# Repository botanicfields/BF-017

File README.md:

# BF-017
タイマーIC 555をディスクリート・トランジスタで作る基板

頒布(Martket place):
https://www.switch-science.com/catalog/6433/

Qiitaに説明があります。
https://qiita.com/BotanicFields/items/ccec29255a49967116c1

GitHubに資料があります。
https://github.com/botanicfields/BF-017

AkiCart:
https://aki.prioris.jp/list/0b58d2fc-eee4-429c-9d86-0e2e1c66c018/

### はじめに
　古典的なタイマーICである555の内部回路を、単体（ディスクリート）トランジスタで実現するプリント基板を作成しました。中国の製造業者がプリント基板を安価かつ短納期で試作してくれます。個人でもプリント基板の設計発注が容易になっていて、555はトレーニングに適切な題材と思いました。

### 工夫点
　オシロスコープによる波形観測を容易にするためにテストポイントを設けます。トランジスタや抵抗などの部品の足やパッドから信号を取り出す必要がなくなり部品を比較的詰めて配置できます。
 
### お詫び
　プリント基板のシルク印刷でQ10, Q11, Q12, Q13の位置を間違えています。幸い、いずれも同じPNPトランジスタなので結果的に組立時には問題にはなりません。
V01L02で修正しました。資料は訂正済のものです。正しくは資料を参照ください。

https://github.com/botanicfields/BF-017/blob/master/BF-017_POS.pdf

### 提供元
BotanicFields, Inc.

https://www.facebook.com/botanicfields/

https://twitter.com/botanicfields

2020年6月22日

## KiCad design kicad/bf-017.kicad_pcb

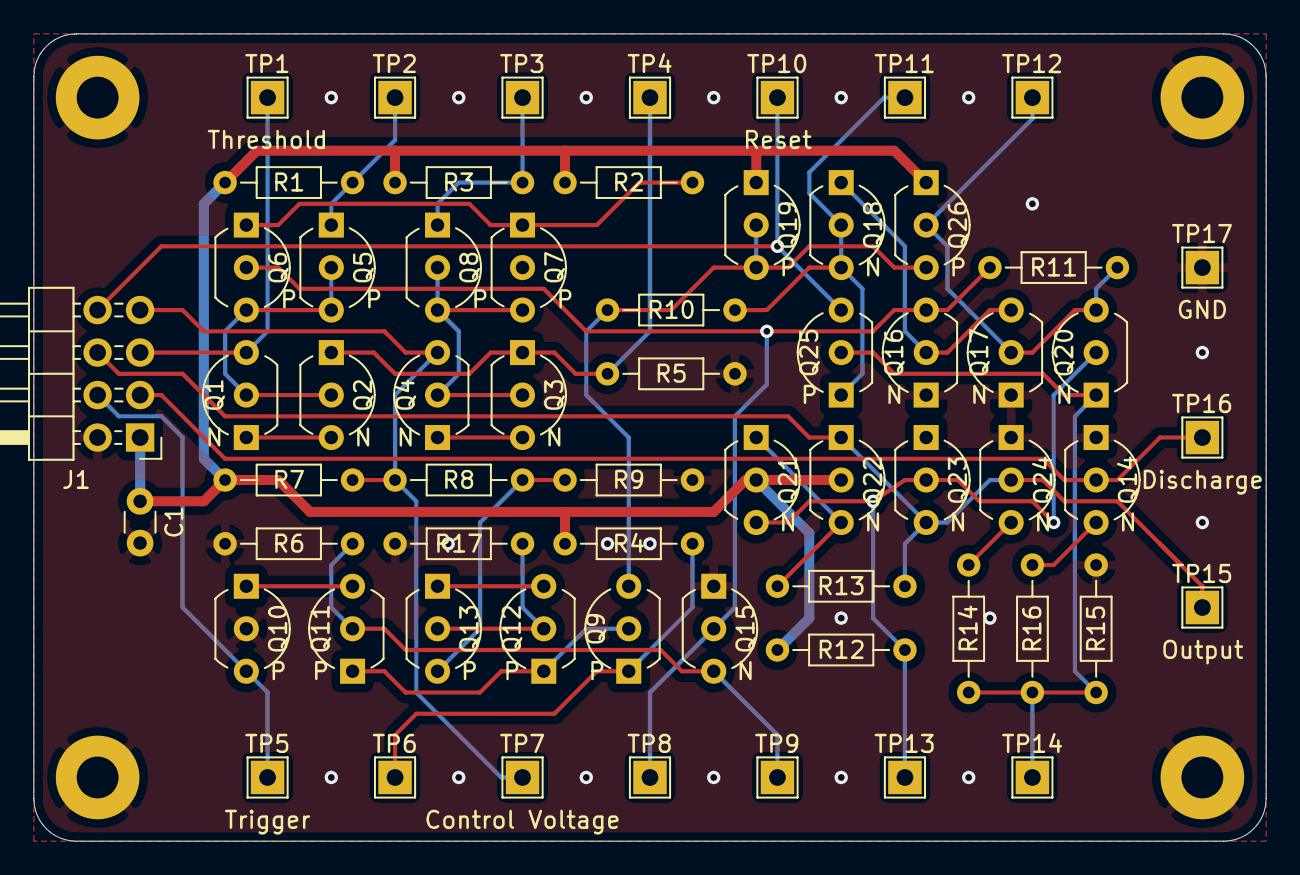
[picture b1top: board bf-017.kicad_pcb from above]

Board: 2 copper layers, 73.7 x 48.3 mm, 62 parts (0 on the bottom side), 33 nets.

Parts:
C1: 100n; C_Disc_D3.0mm_W1.6mm_P2.50mm
J1: 555; PinHeader_2x04_P2.54mm_Horizontal
Q1, Q2, Q3, Q4, Q14, Q15, Q16, Q17, Q18, Q20, Q21, Q22, Q23, Q24: NPN; TO-92_Inline_Wide
Q5, Q6, Q7, Q8, Q9, Q10, Q11, Q12, Q13, Q19, Q25, Q26: PNP; TO-92_Inline_Wide
R1, R3, R11, R15: 4.7k; R_Axial_DIN0204_L3.6mm_D1.6mm_P7.62mm_Horizontal
R2: 820; R_Axial_DIN0204_L3.6mm_D1.6mm_P7.62mm_Horizontal
R4: 1k; R_Axial_DIN0204_L3.6mm_D1.6mm_P7.62mm_Horizontal
R5, R10: 10k; R_Axial_DIN0204_L3.6mm_D1.6mm_P7.62mm_Horizontal
R6: 100k; R_Axial_DIN0204_L3.6mm_D1.6mm_P7.62mm_Horizontal
R7, R8, R9: 5k; R_Axial_DIN0204_L3.6mm_D1.6mm_P7.62mm_Horizontal
R12: 6.8k; R_Axial_DIN0204_L3.6mm_D1.6mm_P7.62mm_Horizontal
R13: 3.9k; R_Axial_DIN0204_L3.6mm_D1.6mm_P7.62mm_Horizontal
R14: 220; R_Axial_DIN0204_L3.6mm_D1.6mm_P7.62mm_Horizontal
R16: 100; R_Axial_DIN0204_L3.6mm_D1.6mm_P7.62mm_Horizontal
R17: 0; R_Axial_DIN0204_L3.6mm_D1.6mm_P7.62mm_Horizontal
TP1, TP2, TP3, TP4, TP5, TP6, TP7, TP8, TP9, TP10, TP11, TP12, TP13, TP14, TP15, TP16, TP17: TestPoint; TestPoint_THTPad_2.0x2.0mm_Drill1.0mm

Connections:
/CONTROL_VOLTAGE: J1.7, Q4.3, R7.2, R8.1, TP7.1
/DISCHARGE: J1.3, Q14.2, TP16.1
/OUTPUT: J1.6, Q22.1, Q23.3, Q24.2, R13.2, TP15.1
/RESET: J1.8, Q25.3, TP10.1
/THRESHOLD: J1.5, Q1.3, TP1.1
/TRIGGER: J1.4, Q10.3, TP5.1
GND: C1.2, J1.2, Q7.2, Q10.2, Q14.1, Q15.1, Q16.1, Q17.1, Q24.1, R5.2, R6.2, R9.2, R15.2, R17.2, TP17.1
unnamed: Q1.1, Q2.3
unnamed: Q1.2, Q2.2, Q5.2, Q5.3, Q6.3
unnamed: Q2.1, Q3.1, R5.1, TP4.1
unnamed: Q3.2, Q4.2, Q7.3, Q8.2, Q8.3
unnamed: Q3.3, Q4.1
unnamed: Q5.1, R1.2, TP2.1
unnamed: Q6.1, Q7.1, R2.2
unnamed: Q8.1, R3.2, TP3.1
unnamed: Q9.1, R4.2, TP6.1
unnamed: Q10.1, Q11.3
unnamed: Q9.2, Q11.1, Q12.1
unnamed: Q11.2, Q15.3, R6.1, TP9.1
unnamed: Q12.2, Q13.2, R17.1
unnamed: Q12.3, Q13.1
unnamed: Q13.3, R8.2, R9.1
unnamed: Q14.3, R16.1
unnamed: Q6.2, Q15.2, Q16.3, R11.1, TP8.1
unnamed: Q16.2, Q17.3, Q18.1
unnamed: Q17.2, Q20.3, Q26.2, R11.2, TP12.1
unnamed: Q18.2, Q18.3, Q25.1, R10.2, TP11.1
unnamed: Q9.3, Q19.2, Q19.3, Q26.3, R10.1
unnamed: Q20.1, Q25.2, R14.2, R15.1, R16.2, TP14.1
unnamed: Q20.2, Q21.3, Q23.2, R12.2, TP13.1
unnamed: Q21.1, Q22.3, R13.1
unnamed: Q24.3, R14.1
VCC: C1.1, J1.1, Q19.1, Q21.2, Q22.2, Q26.1, R1.1, R2.1, R3.1, R4.1, R7.1, R12.1

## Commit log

2021-05-03 add gerber, kicad data
    V01L02

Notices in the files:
kicad/bf-017.kicad_pcb:
Copyright 2020 BotanicFields, Inc.
